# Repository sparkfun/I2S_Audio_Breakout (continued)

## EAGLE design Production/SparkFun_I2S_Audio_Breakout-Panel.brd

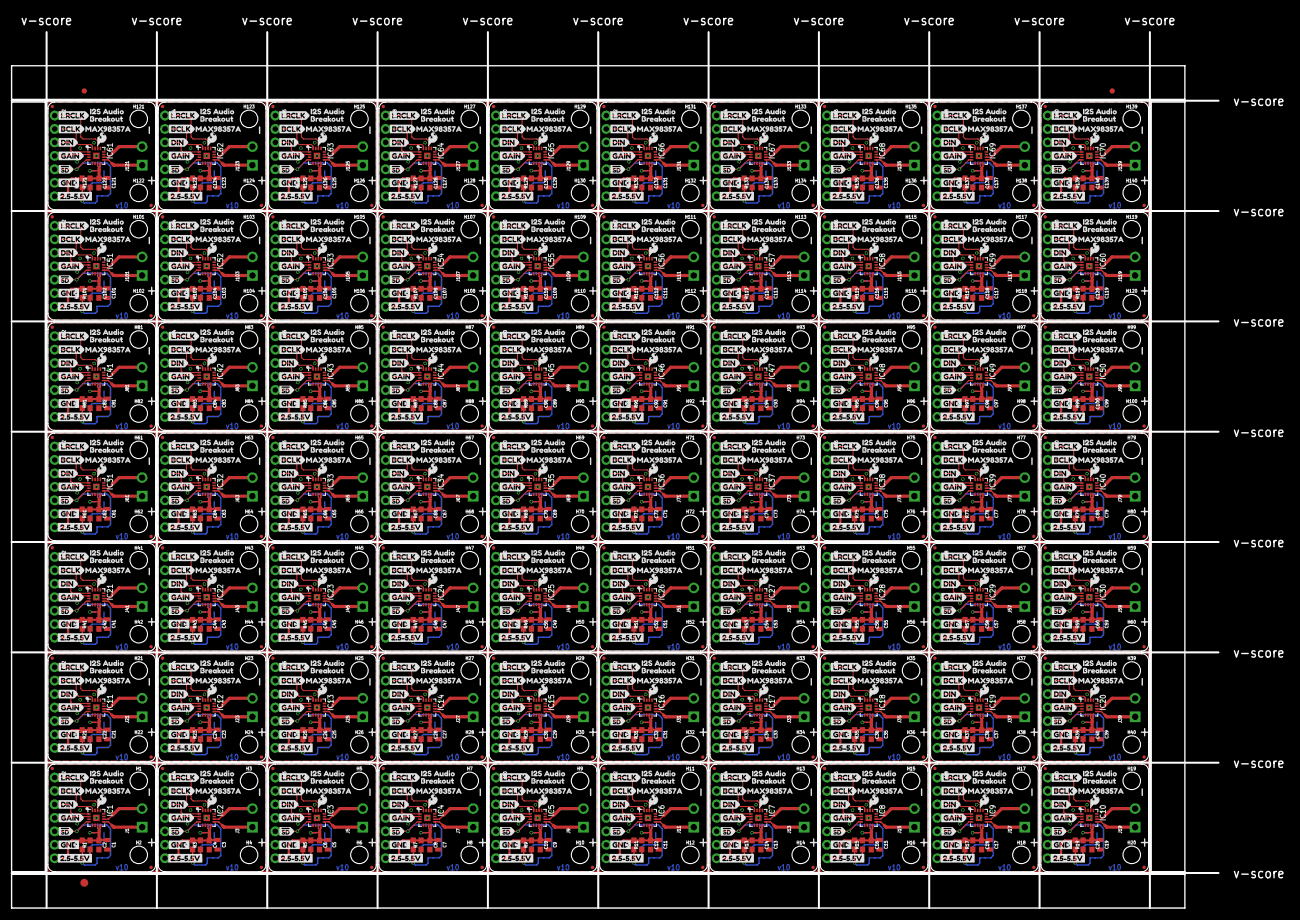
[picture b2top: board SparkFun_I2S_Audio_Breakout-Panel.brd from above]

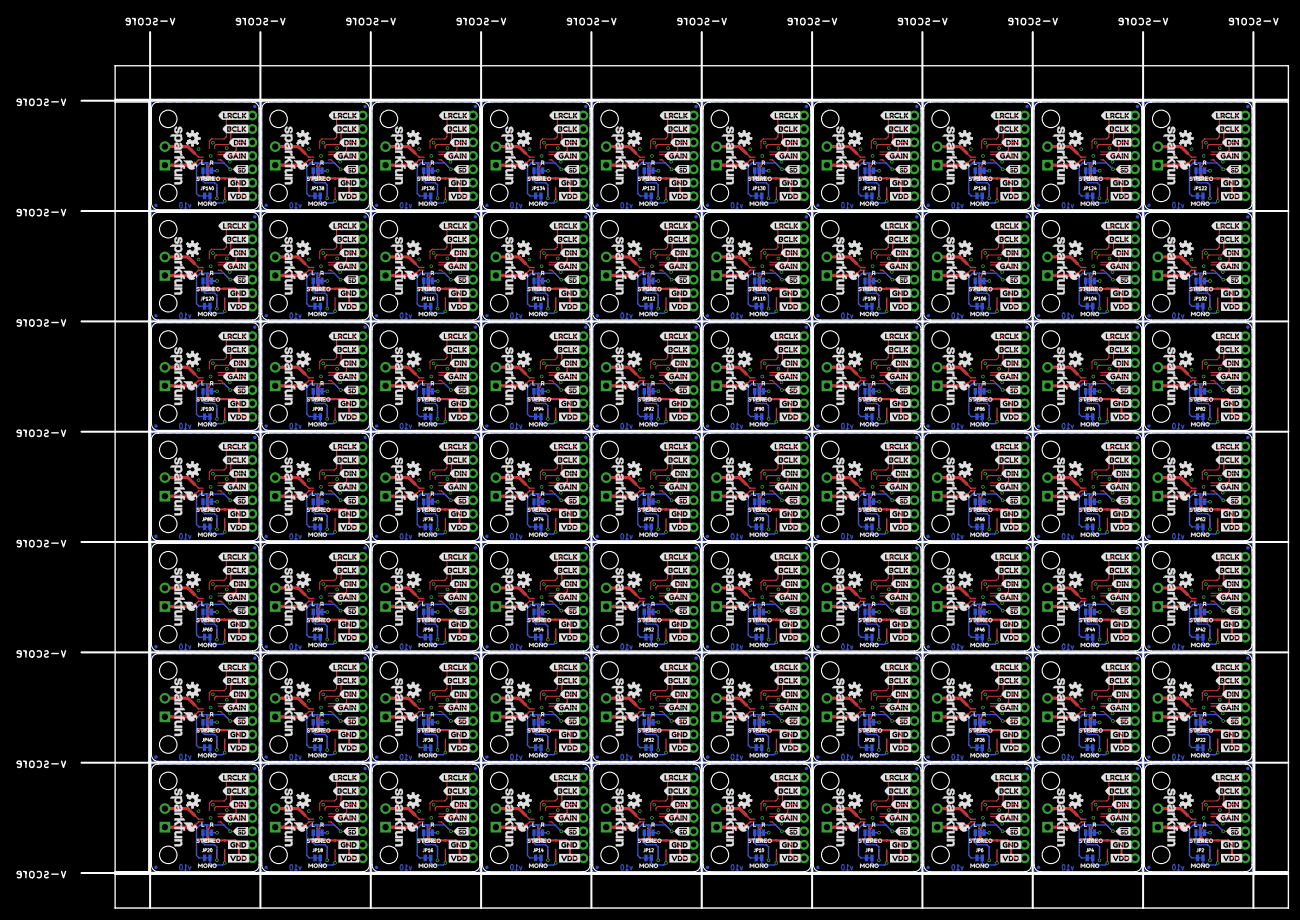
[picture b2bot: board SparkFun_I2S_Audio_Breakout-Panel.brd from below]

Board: 2 copper layers, 227.8 x 165.4 mm, 2733 parts (1190 on the bottom side), 770 nets.

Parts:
C1, C3, C5, C7, C9, C11, C13, C15, C17, C19, C21, C23, C25, C27, C29, C31, C33, C35, C37, C39, C41, C43, C45, C47, C49, C51, C53, C55, C57, C59, C61, C63, C65, C67, C69, C71, C73, C75, C77, C79, C81, C83, C85, C87, C89, C91, C93, C95, C97, C99, C101, C103, C105, C107, C109, C111, C113, C115, C117, C119, C121, C123, C125, C127, C129, C131, C133, C135, C137, C139: 10uF; 0805
C2, C4, C6, C8, C10, C12, C14, C16, C18, C20, C22, C24, C26, C28, C30, C32, C34, C36, C38, C40, C42, C44, C46, C48, C50, C52, C54, C56, C58, C60, C62, C64, C66, C68, C70, C72, C74, C76, C78, C80, C82, C84, C86, C88, C90, C92, C94, C96, C98, C100, C102, C104, C106, C108, C110, C112, C114, C116, C118, C120, C122, C124, C126, C128, C130, C132, C134, C136, C138, C140: 0.1uF; 0603
E$1, E$2: FIDUCIAL-1X2
E$3: FIDUCIAL-1.5X3
FD1, FD2, FD3, FD4, FD5, FD6, FD7, FD8, FD9, FD10, FD11, FD12, FD13, FD14, FD15, FD16, FD17, FD18, FD19, FD20, FD21, FD22, FD23, FD24, FD25, FD26, FD27, FD28, FD29, FD30, FD31, FD32, FD33, FD34, FD35, FD36, FD37, FD38, FD39, FD40, FD41, FD42, FD43, FD44, FD45, FD46, FD47, FD48, FD49, FD50, FD51, FD52, FD53, FD54, FD55, FD56, FD57, FD58, FD59, FD60, FD61, FD62, FD63, FD64, FD65, FD66, FD67, FD68, FD69, FD70, FD71, FD72, FD73, FD74, FD75, FD76, FD77, FD78, FD79, FD80, FD81, FD82, FD83, FD84, FD85, FD86, FD87, FD88, FD89, FD90, FD91, FD92, FD93, FD94, FD95, FD96, FD97, FD98, FD99, FD100, FD101, FD102, FD103, FD104, FD105, FD106, FD107, FD108, FD109, FD110, FD111, FD112, FD113, FD114, FD115, FD116, FD117, FD118, FD119, FD120, FD121, FD122, FD123, FD124, FD125, FD126, FD127, FD128, FD129, FD130, FD131, FD132, FD133, FD134, FD135, FD136, FD137, FD138, FD139, FD140, FD141, FD142, FD143, FD144, FD145, FD146, FD147, FD148, FD149, FD150, FD151, FD152, FD153, FD154, FD155, FD156, FD157, FD158, FD159, FD160, FD161, FD162, FD163, FD164, FD165, FD166, FD167, FD168, FD169, FD170, FD171, FD172, FD173, FD174, FD175, FD176, FD177, FD178, FD179, FD180, FD181, FD182, FD183, FD184, FD185, FD186, FD187, FD188, FD189, FD190, FD191, FD192, FD193, FD194, FD195, FD196, FD197, FD198, FD199, FD200, FD201, FD202, FD203, FD204, FD205, FD206, FD207, FD208, FD209, FD210, FD211, FD212, FD213, FD214, FD215, FD216, FD217, FD218, FD219, FD220, FD221, FD222, FD223, FD224, FD225, FD226, FD227, FD228, FD229, FD230, FD231, FD232, FD233, FD234, FD235, FD236, FD237, FD238, FD239, FD240, FD241, FD242, FD243, FD244, FD245, FD246, FD247, FD248, FD249, FD250, FD251, FD252, FD253, FD254, FD255, FD256, FD257, FD258, FD259, FD260, FD261, FD262, FD263, FD264, FD265, FD266, FD267, FD268, FD269, FD270, FD271, FD272, FD273, FD274, FD275, FD276, FD277, FD278, FD279, FD280: FIDUCIALUFIDUCIAL; FIDUCIAL-MICRO
H1, H2, H3, H4, H5, H6, H7, H8, H9, H10, H11, H12, H13, H14, H15, H16, H17, H18, H19, H20, H21, H22, H23, H24, H25, H26, H27, H28, H29, H30, H31, H32, H33, H34, H35, H36, H37, H38, H39, H40, H41, H42, H43, H44, H45, H46, H47, H48, H49, H50, H51, H52, H53, H54, H55, H56, H57, H58, H59, H60, H61, H62, H63, H64, H65, H66, H67, H68, H69, H70, H71, H72, H73, H74, H75, H76, H77, H78, H79, H80, H81, H82, H83, H84, H85, H86, H87, H88, H89, H90, H91, H92, H93, H94, H95, H96, H97, H98, H99, H100, H101, H102, H103, H104, H105, H106, H107, H108, H109, H110, H111, H112, H113, H114, H115, H116, H117, H118, H119, H120, H121, H122, H123, H124, H125, H126, H127, H128, H129, H130, H131, H132, H133, H134, H135, H136, H137, H138, H139, H140: STAND-OFF
IC1, IC2, IC3, IC4, IC5, IC6, IC7, IC8, IC9, IC10, IC11, IC12, IC13, IC14, IC15, IC16, IC17, IC18, IC19, IC20, IC21, IC22, IC23, IC24, IC25, IC26, IC27, IC28, IC29, IC30, IC31, IC32, IC33, IC34, IC35, IC36, IC37, IC38, IC39, IC40, IC41, IC42, IC43, IC44, IC45, IC46, IC47, IC48, IC49, IC50, IC51, IC52, IC53, IC54, IC55, IC56, IC57, IC58, IC59, IC60, IC61, IC62, IC63, IC64, IC65, IC66, IC67, IC68, IC69, IC70: MAX98375A; TQFN-16
J1, J3, J5, J7, J9, J11, J13, J15, J17, J19, J21, J23, J25, J27, J29, J31, J33, J35, J37, J39, J41, J43, J45, J47, J49, J51, J53, J55, J57, J59, J61, J63, J65, J67, J69, J71, J73, J75, J77, J79, J81, J83, J85, J87, J89, J91, J93, J95, J97, J99, J101, J103, J105, J107, J109, J111, J113, J115, J117, J119, J121, J123, J125, J127, J129, J131, J133, J135, J137, J139: SCREWTERMINAL-3.5MM-2-NS
J2, J4, J6, J8, J10, J12, J14, J16, J18, J20, J22, J24, J26, J28, J30, J32, J34, J36, J38, J40, J42, J44, J46, J48, J50, J52, J54, J56, J58, J60, J62, J64, J66, J68, J70, J72, J74, J76, J78, J80, J82, J84, J86, J88, J90, J92, J94, J96, J98, J100, J102, J104, J106, J108, J110, J112, J114, J116, J118, J120, J122, J124, J126, J128, J130, J132, J134, J136, J138, J140: 1X07_NO_SILK
JP1, JP3, JP5, JP7, JP9, JP11, JP13, JP15, JP17, JP19, JP21, JP23, JP25, JP27, JP29, JP31, JP33, JP35, JP37, JP39, JP41, JP43, JP45, JP47, JP49, JP51, JP53, JP55, JP57, JP59, JP61, JP63, JP65, JP67, JP69, JP71, JP73, JP75, JP77, JP79, JP81, JP83, JP85, JP87, JP89, JP91, JP93, JP95, JP97, JP99, JP101, JP103, JP105, JP107, JP109, JP111, JP113, JP115, JP117, JP119, JP121, JP123, JP125, JP127, JP129, JP131, JP133, JP135, JP137, JP139: SMT-JUMPER_3_NO_NO-SILK
JP2, JP4, JP6, JP8, JP10, JP12, JP14, JP16, JP18, JP20, JP22, JP24, JP26, JP28, JP30, JP32, JP34, JP36, JP38, JP40, JP42, JP44, JP46, JP48, JP50, JP52, JP54, JP56, JP58, JP60, JP62, JP64, JP66, JP68, JP70, JP72, JP74, JP76, JP78, JP80, JP82, JP84, JP86, JP88, JP90, JP92, JP94, JP96, JP98, JP100, JP102, JP104, JP106, JP108, JP110, JP112, JP114, JP116, JP118, JP120, JP122, JP124, JP126, JP128, JP130, JP132, JP134, JP136, JP138, JP140: SMT-JUMPER_2_NC_TRACE_NO-SILK
LOGO1, LOGO3, LOGO5, LOGO7, LOGO9, LOGO11, LOGO13, LOGO15, LOGO17, LOGO19, LOGO21, LOGO23, LOGO25, LOGO27, LOGO29, LOGO31, LOGO33, LOGO35, LOGO37, LOGO39, LOGO41, LOGO43, LOGO45, LOGO47, LOGO49, LOGO51, LOGO53, LOGO55, LOGO57, LOGO59, LOGO61, LOGO63, LOGO65, LOGO67, LOGO69, LOGO71, LOGO73, LOGO75, LOGO77, LOGO79, LOGO81, LOGO83, LOGO85, LOGO87, LOGO89, LOGO91, LOGO93, LOGO95, LOGO97, LOGO99, LOGO101, LOGO103, LOGO105, LOGO107, LOGO109, LOGO111, LOGO113, LOGO115, LOGO117, LOGO119, LOGO121, LOGO123, LOGO125, LOGO127, LOGO129, LOGO131, LOGO133, LOGO135, LOGO137, LOGO139: SFE_LOGO_NAME_FLAME.1_INCH; SFE_LOGO_NAME_FLAME_.1
LOGO2, LOGO4, LOGO6, LOGO8, LOGO10, LOGO12, LOGO14, LOGO16, LOGO18, LOGO20, LOGO22, LOGO24, LOGO26, LOGO28, LOGO30, LOGO32, LOGO34, LOGO36, LOGO38, LOGO40, LOGO42, LOGO44, LOGO46, LOGO48, LOGO50, LOGO52, LOGO54, LOGO56, LOGO58, LOGO60, LOGO62, LOGO64, LOGO66, LOGO68, LOGO70, LOGO72, LOGO74, LOGO76, LOGO78, LOGO80, LOGO82, LOGO84, LOGO86, LOGO88, LOGO90, LOGO92, LOGO94, LOGO96, LOGO98, LOGO100, LOGO102, LOGO104, LOGO106, LOGO108, LOGO110, LOGO112, LOGO114, LOGO116, LOGO118, LOGO120, LOGO122, LOGO124, LOGO126, LOGO128, LOGO130, LOGO132, LOGO134, LOGO136, LOGO138, LOGO140: OSHW-LOGOS; OSHW-LOGO-S
R1, R3, R5, R7, R9, R11, R13, R15, R17, R19, R21, R23, R25, R27, R29, R31, R33, R35, R37, R39, R41, R43, R45, R47, R49, R51, R53, R55, R57, R59, R61, R63, R65, R67, R69, R71, R73, R75, R77, R79, R81, R83, R85, R87, R89, R91, R93, R95, R97, R99, R101, R103, R105, R107, R109, R111, R113, R115, R117, R119, R121, R123, R125, R127, R129, R131, R133, R135, R137, R139: 300k; 0603
R2, R4, R6, R8, R10, R12, R14, R16, R18, R20, R22, R24, R26, R28, R30, R32, R34, R36, R38, R40, R42, R44, R46, R48, R50, R52, R54, R56, R58, R60, R62, R64, R66, R68, R70, R72, R74, R76, R78, R80, R82, R84, R86, R88, R90, R92, R94, R96, R98, R100, R102, R104, R106, R108, R110, R112, R114, R116, R118, R120, R122, R124, R126, R128, R130, R132, R134, R136, R138, R140: 1M; 0603
U$1, U$24, U$46, U$68, U$90, U$112, U$134, U$156, U$178, U$200, U$222, U$244, U$266, U$288, U$310, U$332, U$354, U$376, U$398, U$420, U$442, U$464, U$486, U$508, U$530, U$552, U$574, U$596, U$618, U$640, U$662, U$684, U$706, U$728, U$750, U$772, U$794, U$816, U$838, U$860, U$882, U$904, U$926, U$948, U$970, U$992, U$1014, U$1036, U$1058, U$1080, U$1102, U$1124, U$1146, U$1168, U$1190, U$1212, U$1234, U$1256, U$1278, U$1300, U$1322, U$1344, U$1366, U$1388, U$1410, U$1432, U$1454, U$1476, U$1498, U$1520: 2#5#5#5V13
U$2, U$23, U$25, U$39, U$47, U$61, U$69, U$83, U$91, U$105, U$113, U$127, U$135, U$149, U$157, U$171, U$179, U$193, U$201, U$215, U$223, U$237, U$245, U$259, U$267, U$281, U$289, U$303, U$311, U$325, U$333, U$347, U$355, U$369, U$377, U$391, U$399, U$413, U$421, U$435, U$443, U$457, U$465, U$479, U$487, U$501, U$509, U$523, U$531, U$545, U$553, U$567, U$575, U$589, U$597, U$611, U$619, U$633, U$641, U$655, U$663, U$677, U$685, U$699, U$707, U$721, U$729, U$743, U$751, U$765, U$773, U$787, U$795, U$809, U$817, U$831, U$839, U$853, U$861, U$875, U$883, U$897, U$905, U$919, U$927, U$941, U$949, U$963, U$971, U$985, U$993, U$1007, U$1015, U$1029, U$1037, U$1051, U$1059, U$1073, U$1081, U$1095, U$1103, U$1117, U$1125, U$1139, U$1147, U$1161, U$1169, U$1183, U$1191, U$1205, U$1213, U$1227, U$1235, U$1249, U$1257, U$1271, U$1279, U$1293, U$1301, U$1315, U$1323, U$1337, U$1345, U$1359, U$1367, U$1381, U$1389, U$1403, U$1411, U$1425, U$1433, U$1447, U$1455, U$1469, U$1477, U$1491, U$1499, U$1513, U$1521, U$1535: GND9
U$3, U$26, U$48, U$70, U$92, U$114, U$136, U$158, U$180, U$202, U$224, U$246, U$268, U$290, U$312, U$334, U$356, U$378, U$400, U$422, U$444, U$466, U$488, U$510, U$532, U$554, U$576, U$598, U$620, U$642, U$664, U$686, U$708, U$730, U$752, U$774, U$796, U$818, U$840, U$862, U$884, U$906, U$928, U$950, U$972, U$994, U$1016, U$1038, U$1060, U$1082, U$1104, U$1126, U$1148, U$1170, U$1192, U$1214, U$1236, U$1258, U$1280, U$1302, U$1324, U$1346, U$1368, U$1390, U$1412, U$1434, U$1456, U$1478, U$1500, U$1522: #SD7
U$4, U$27, U$49, U$71, U$93, U$115, U$137, U$159, U$181, U$203, U$225, U$247, U$269, U$291, U$313, U$335, U$357, U$379, U$401, U$423, U$445, U$467, U$489, U$511, U$533, U$555, U$577, U$599, U$621, U$643, U$665, U$687, U$709, U$731, U$753, U$775, U$797, U$819, U$841, U$863, U$885, U$907, U$929, U$951, U$973, U$995, U$1017, U$1039, U$1061, U$1083, U$1105, U$1127, U$1149, U$1171, U$1193, U$1215, U$1237, U$1259, U$1281, U$1303, U$1325, U$1347, U$1369, U$1391, U$1413, U$1435, U$1457, U$1479, U$1501, U$1523: GAIN6
U$5, U$28, U$50, U$72, U$94, U$116, U$138, U$160, U$182, U$204, U$226, U$248, U$270, U$292, U$314, U$336, U$358, U$380, U$402, U$424, U$446, U$468, U$490, U$512, U$534, U$556, U$578, U$600, U$622, U$644, U$666, U$688, U$710, U$732, U$754, U$776, U$798, U$820, U$842, U$864, U$886, U$908, U$930, U$952, U$974, U$996, U$1018, U$1040, U$1062, U$1084, U$1106, U$1128, U$1150, U$1172, U$1194, U$1216, U$1238, U$1260, U$1282, U$1304, U$1326, U$1348, U$1370, U$1392, U$1414, U$1436, U$1458, U$1480, U$1502, U$1524: DIN5
U$6, U$29, U$51, U$73, U$95, U$117, U$139, U$161, U$183, U$205, U$227, U$249, U$271, U$293, U$315, U$337, U$359, U$381, U$403, U$425, U$447, U$469, U$491, U$513, U$535, U$557, U$579, U$601, U$623, U$645, U$667, U$689, U$711, U$733, U$755, U$777, U$799, U$821, U$843, U$865, U$887, U$909, U$931, U$953, U$975, U$997, U$1019, U$1041, U$1063, U$1085, U$1107, U$1129, U$1151, U$1173, U$1195, U$1217, U$1239, U$1261, U$1283, U$1305, U$1327, U$1349, U$1371, U$1393, U$1415, U$1437, U$1459, U$1481, U$1503, U$1525: BCLK4
U$7, U$30, U$52, U$74, U$96, U$118, U$140, U$162, U$184, U$206, U$228, U$250, U$272, U$294, U$316, U$338, U$360, U$382, U$404, U$426, U$448, U$470, U$492, U$514, U$536, U$558, U$580, U$602, U$624, U$646, U$668, U$690, U$712, U$734, U$756, U$778, U$800, U$822, U$844, U$866, U$888, U$910, U$932, U$954, U$976, U$998, U$1020, U$1042, U$1064, U$1086, U$1108, U$1130, U$1152, U$1174, U$1196, U$1218, U$1240, U$1262, U$1284, U$1306, U$1328, U$1350, U$1372, U$1394, U$1416, U$1438, U$1460, U$1482, U$1504, U$1526: LRCLK3
U$8, U$31, U$53, U$75, U$97, U$119, U$141, U$163, U$185, U$207, U$229, U$251, U$273, U$295, U$317, U$339, U$361, U$383, U$405, U$427, U$449, U$471, U$493, U$515, U$537, U$559, U$581, U$603, U$625, U$647, U$669, U$691, U$713, U$735, U$757, U$779, U$801, U$823, U$845, U$867, U$889, U$911, U$933, U$955, U$977, U$999, U$1021, U$1043, U$1065, U$1087, U$1109, U$1131, U$1153, U$1175, U$1197, U$1219, U$1241, U$1263, U$1285, U$1307, U$1329, U$1351, U$1373, U$1395, U$1417, U$1439, U$1461, U$1483, U$1505, U$1527: I2S_AUDIO0
U$9, U$32, U$54, U$76, U$98, U$120, U$142, U$164, U$186, U$208, U$230, U$252, U$274, U$296, U$318, U$340, U$362, U$384, U$406, U$428, U$450, U$472, U$494, U$516, U$538, U$560, U$582, U$604, U$626, U$648, U$670, U$692, U$714, U$736, U$758, U$780, U$802, U$824, U$846, U$868, U$890, U$912, U$934, U$956, U$978, U$1000, U$1022, U$1044, U$1066, U$1088, U$1110, U$1132, U$1154, U$1176, U$1198, U$1220, U$1242, U$1264, U$1286, U$1308, U$1330, U$1352, U$1374, U$1396, U$1418, U$1440, U$1462, U$1484, U$1506, U$1528: BREAKOUT1
U$10, U$33, U$55, U$77, U$99, U$121, U$143, U$165, U$187, U$209, U$231, U$253, U$275, U$297, U$319, U$341, U$363, U$385, U$407, U$429, U$451, U$473, U$495, U$517, U$539, U$561, U$583, U$605, U$627, U$649, U$671, U$693, U$715, U$737, U$759, U$781, U$803, U$825, U$847, U$869, U$891, U$913, U$935, U$957, U$979, U$1001, U$1023, U$1045, U$1067, U$1089, U$1111, U$1133, U$1155, U$1177, U$1199, U$1221, U$1243, U$1265, U$1287, U$1309, U$1331, U$1353, U$1375, U$1397, U$1419, U$1441, U$1463, U$1485, U$1507, U$1529: MAX98357A2
U$11, U$40, U$62, U$84, U$106, U$128, U$150, U$172, U$194, U$216, U$238, U$260, U$282, U$304, U$326, U$348, U$370, U$392, U$414, U$436, U$458, U$480, U$502, U$524, U$546, U$568, U$590, U$612, U$634, U$656, U$678, U$700, U$722, U$744, U$766, U$788, U$810, U$832, U$854, U$876, U$898, U$920, U$942, U$964, U$986, U$1008, U$1030, U$1052, U$1074, U$1096, U$1118, U$1140, U$1162, U$1184, U$1206, U$1228, U$1250, U$1272, U$1294, U$1316, U$1338, U$1360, U$1382, U$1404, U$1426, U$1448, U$1470, U$1492, U$1514, U$1536: LRCLK0
U$12, U$41, U$63, U$85, U$107, U$129, U$151, U$173, U$195, U$217, U$239, U$261, U$283, U$305, U$327, U$349, U$371, U$393, U$415, U$437, U$459, U$481, U$503, U$525, U$547, U$569, U$591, U$613, U$635, U$657, U$679, U$701, U$723, U$745, U$767, U$789, U$811, U$833, U$855, U$877, U$899, U$921, U$943, U$965, U$987, U$1009, U$1031, U$1053, U$1075, U$1097, U$1119, U$1141, U$1163, U$1185, U$1207, U$1229, U$1251, U$1273, U$1295, U$1317, U$1339, U$1361, U$1383, U$1405, U$1427, U$1449, U$1471, U$1493, U$1515, U$1537: BCLK1
U$13, U$42, U$64, U$86, U$108, U$130, U$152, U$174, U$196, U$218, U$240, U$262, U$284, U$306, U$328, U$350, U$372, U$394, U$416, U$438, U$460, U$482, U$504, U$526, U$548, U$570, U$592, U$614, U$636, U$658, U$680, U$702, U$724, U$746, U$768, U$790, U$812, U$834, U$856, U$878, U$900, U$922, U$944, U$966, U$988, U$1010, U$1032, U$1054, U$1076, U$1098, U$1120, U$1142, U$1164, U$1186, U$1208, U$1230, U$1252, U$1274, U$1296, U$1318, U$1340, U$1362, U$1384, U$1406, U$1428, U$1450, U$1472, U$1494, U$1516, U$1538: DIN2
U$14, U$43, U$65, U$87, U$109, U$131, U$153, U$175, U$197, U$219, U$241, U$263, U$285, U$307, U$329, U$351, U$373, U$395, U$417, U$439, U$461, U$483, U$505, U$527, U$549, U$571, U$593, U$615, U$637, U$659, U$681, U$703, U$725, U$747, U$769, U$791, U$813, U$835, U$857, U$879, U$901, U$923, U$945, U$967, U$989, U$1011, U$1033, U$1055, U$1077, U$1099, U$1121, U$1143, U$1165, U$1187, U$1209, U$1231, U$1253, U$1275, U$1297, U$1319, U$1341, U$1363, U$1385, U$1407, U$1429, U$1451, U$1473, U$1495, U$1517, U$1539: GAIN3
U$15, U$21, U$45, U$67, U$89, U$111, U$133, U$155, U$177, U$199, U$221, U$243, U$265, U$287, U$309, U$331, U$353, U$375, U$397, U$419, U$441, U$463, U$485, U$507, U$529, U$551, U$573, U$595, U$617, U$639, U$661, U$683, U$705, U$727, U$749, U$771, U$793, U$815, U$837, U$859, U$881, U$903, U$925, U$947, U$969, U$991, U$1013, U$1035, U$1057, U$1079, U$1101, U$1123, U$1145, U$1167, U$1189, U$1211, U$1233, U$1255, U$1277, U$1299, U$1321, U$1343, U$1365, U$1387, U$1409, U$1431, U$1453, U$1475, U$1497, U$1519: SFE_LOGO_FLAME_.1
U$16, U$35, U$57, U$79, U$101, U$123, U$145, U$167, U$189, U$211, U$233, U$255, U$277, U$299, U$321, U$343, U$365, U$387, U$409, U$431, U$453, U$475, U$497, U$519, U$541, U$563, U$585, U$607, U$629, U$651, U$673, U$695, U$717, U$739, U$761, U$783, U$805, U$827, U$849, U$871, U$893, U$915, U$937, U$959, U$981, U$1003, U$1025, U$1047, U$1069, U$1091, U$1113, U$1135, U$1157, U$1179, U$1201, U$1223, U$1245, U$1267, U$1289, U$1311, U$1333, U$1355, U$1377, U$1399, U$1421, U$1443, U$1465, U$1487, U$1509, U$1531: MONO12
U$17, U$37, U$59, U$81, U$103, U$125, U$147, U$169, U$191, U$213, U$235, U$257, U$279, U$301, U$323, U$345, U$367, U$389, U$411, U$433, U$455, U$477, U$499, U$521, U$543, U$565, U$587, U$609, U$631, U$653, U$675, U$697, U$719, U$741, U$763, U$785, U$807, U$829, U$851, U$873, U$895, U$917, U$939, U$961, U$983, U$1005, U$1027, U$1049, U$1071, U$1093, U$1115, U$1137, U$1159, U$1181, U$1203, U$1225, U$1247, U$1269, U$1291, U$1313, U$1335, U$1357, U$1379, U$1401, U$1423, U$1445, U$1467, U$1489, U$1511, U$1533: L10
U$18, U$38, U$60, U$82, U$104, U$126, U$148, U$170, U$192, U$214, U$236, U$258, U$280, U$302, U$324, U$346, U$368, U$390, U$412, U$434, U$456, U$478, U$500, U$522, U$544, U$566, U$588, U$610, U$632, U$654, U$676, U$698, U$720, U$742, U$764, U$786, U$808, U$830, U$852, U$874, U$896, U$918, U$940, U$962, U$984, U$1006, U$1028, U$1050, U$1072, U$1094, U$1116, U$1138, U$1160, U$1182, U$1204, U$1226, U$1248, U$1270, U$1292, U$1314, U$1336, U$1358, U$1380, U$1402, U$1424, U$1446, U$1468, U$1490, U$1512, U$1534: R11
U$19, U$36, U$58, U$80, U$102, U$124, U$146, U$168, U$190, U$212, U$234, U$256, U$278, U$300, U$322, U$344, U$366, U$388, U$410, U$432, U$454, U$476, U$498, U$520, U$542, U$564, U$586, U$608, U$630, U$652, U$674, U$696, U$718, U$740, U$762, U$784, U$806, U$828, U$850, U$872, U$894, U$916, U$938, U$960, U$982, U$1004, U$1026, U$1048, U$1070, U$1092, U$1114, U$1136, U$1158, U$1180, U$1202, U$1224, U$1246, U$1268, U$1290, U$1312, U$1334, U$1356, U$1378, U$1400, U$1422, U$1444, U$1466, U$1488, U$1510, U$1532: STEREO14
U$20, U$44, U$66, U$88, U$110, U$132, U$154, U$176, U$198, U$220, U$242, U$264, U$286, U$308, U$330, U$352, U$374, U$396, U$418, U$440, U$462, U$484, U$506, U$528, U$550, U$572, U$594, U$616, U$638, U$660, U$682, U$704, U$726, U$748, U$770, U$792, U$814, U$836, U$858, U$880, U$902, U$924, U$946, U$968, U$990, U$1012, U$1034, U$1056, U$1078, U$1100, U$1122, U$1144, U$1166, U$1188, U$1210, U$1232, U$1254, U$1276, U$1298, U$1320, U$1342, U$1364, U$1386, U$1408, U$1430, U$1452, U$1474, U$1496, U$1518, U$1540: #SD4
U$22, U$34, U$56, U$78, U$100, U$122, U$144, U$166, U$188, U$210, U$232, U$254, U$276, U$298, U$320, U$342, U$364, U$386, U$408, U$430, U$452, U$474, U$496, U$518, U$540, U$562, U$584, U$606, U$628, U$650, U$672, U$694, U$716, U$738, U$760, U$782, U$804, U$826, U$848, U$870, U$892, U$914, U$936, U$958, U$980, U$1002, U$1024, U$1046, U$1068, U$1090, U$1112, U$1134, U$1156, U$1178, U$1200, U$1222, U$1244, U$1266, U$1288, U$1310, U$1332, U$1354, U$1376, U$1398, U$1420, U$1442, U$1464, U$1486, U$1508, U$1530: VDD8

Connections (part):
!SD: IC1.P$4, J2.5, JP1.2, JP2.1
!SD1: IC2.P$4, J4.5, JP3.2, JP4.1
!SD2: IC3.P$4, J6.5, JP5.2, JP6.1
!SD3: IC4.P$4, J8.5, JP7.2, JP8.1
!SD4: IC5.P$4, J10.5, JP9.2, JP10.1
!SD5: IC6.P$4, J12.5, JP11.2, JP12.1
!SD6: IC7.P$4, J14.5, JP13.2, JP14.1
!SD7: IC8.P$4, J16.5, JP15.2, JP16.1
!SD8: IC9.P$4, J18.5, JP17.2, JP18.1
!SD9: IC10.P$4, J20.5, JP19.2, JP20.1
!SD10: IC11.P$4, J22.5, JP21.2, JP22.1
!SD11: IC12.P$4, J24.5, JP23.2, JP24.1
!SD12: IC13.P$4, J26.5, JP25.2, JP26.1
!SD13: IC14.P$4, J28.5, JP27.2, JP28.1
!SD14: IC15.P$4, J30.5, JP29.2, JP30.1
!SD15: IC16.P$4, J32.5, JP31.2, JP32.1
!SD16: IC17.P$4, J34.5, JP33.2, JP34.1
!SD17: IC18.P$4, J36.5, JP35.2, JP36.1
!SD18: IC19.P$4, J38.5, JP37.2, JP38.1
!SD19: IC20.P$4, J40.5, JP39.2, JP40.1
!SD20: IC21.P$4, J42.5, JP41.2, JP42.1
!SD21: IC22.P$4, J44.5, JP43.2, JP44.1
!SD22: IC23.P$4, J46.5, JP45.2, JP46.1
!SD23: IC24.P$4, J48.5, JP47.2, JP48.1
!SD24: IC25.P$4, J50.5, JP49.2, JP50.1
!SD25: IC26.P$4, J52.5, JP51.2, JP52.1
!SD26: IC27.P$4, J54.5, JP53.2, JP54.1
!SD27: IC28.P$4, J56.5, JP55.2, JP56.1
!SD28: IC29.P$4, J58.5, JP57.2, JP58.1
!SD29: IC30.P$4, J60.5, JP59.2, JP60.1
!SD30: IC31.P$4, J62.5, JP61.2, JP62.1
!SD31: IC32.P$4, J64.5, JP63.2, JP64.1
!SD32: IC33.P$4, J66.5, JP65.2, JP66.1
!SD33: IC34.P$4, J68.5, JP67.2, JP68.1
!SD34: IC35.P$4, J70.5, JP69.2, JP70.1
!SD35: IC36.P$4, J72.5, JP71.2, JP72.1
!SD36: IC37.P$4, J74.5, JP73.2, JP74.1
!SD37: IC38.P$4, J76.5, JP75.2, JP76.1
!SD38: IC39.P$4, J78.5, JP77.2, JP78.1
!SD39: IC40.P$4, J80.5, JP79.2, JP80.1
!SD40: IC41.P$4, J82.5, JP81.2, JP82.1
!SD41: IC42.P$4, J84.5, JP83.2, JP84.1
!SD42: IC43.P$4, J86.5, JP85.2, JP86.1
!SD43: IC44.P$4, J88.5, JP87.2, JP88.1
!SD44: IC45.P$4, J90.5, JP89.2, JP90.1
!SD45: IC46.P$4, J92.5, JP91.2, JP92.1
!SD46: IC47.P$4, J94.5, JP93.2, JP94.1
!SD47: IC48.P$4, J96.5, JP95.2, JP96.1
!SD48: IC49.P$4, J98.5, JP97.2, JP98.1
!SD49: IC50.P$4, J100.5, JP99.2, JP100.1
!SD50: IC51.P$4, J102.5, JP101.2, JP102.1
!SD51: IC52.P$4, J104.5, JP103.2, JP104.1
!SD52: IC53.P$4, J106.5, JP105.2, JP106.1
!SD53: IC54.P$4, J108.5, JP107.2, JP108.1
!SD54: IC55.P$4, J110.5, JP109.2, JP110.1
!SD55: IC56.P$4, J112.5, JP111.2, JP112.1
!SD56: IC57.P$4, J114.5, JP113.2, JP114.1
!SD57: IC58.P$4, J116.5, JP115.2, JP116.1
!SD58: IC59.P$4, J118.5, JP117.2, JP118.1
!SD59: IC60.P$4, J120.5, JP119.2, JP120.1
!SD60: IC61.P$4, J122.5, JP121.2, JP122.1
!SD61: IC62.P$4, J124.5, JP123.2, JP124.1
!SD62: IC63.P$4, J126.5, JP125.2, JP126.1
!SD63: IC64.P$4, J128.5, JP127.2, JP128.1
!SD64: IC65.P$4, J130.5, JP129.2, JP130.1
!SD65: IC66.P$4, J132.5, JP131.2, JP132.1
!SD66: IC67.P$4, J134.5, JP133.2, JP134.1
!SD67: IC68.P$4, J136.5, JP135.2, JP136.1
!SD68: IC69.P$4, J138.5, JP137.2, JP138.1
!SD69: IC70.P$4, J140.5, JP139.2, JP140.1
BCLK: IC1.P$16, J2.2
BCLK1: IC2.P$16, J4.2
BCLK2: IC3.P$16, J6.2
BCLK3: IC4.P$16, J8.2
BCLK4: IC5.P$16, J10.2
BCLK5: IC6.P$16, J12.2
BCLK6: IC7.P$16, J14.2
BCLK7: IC8.P$16, J16.2
BCLK8: IC9.P$16, J18.2
BCLK9: IC10.P$16, J20.2
BCLK10: IC11.P$16, J22.2
BCLK11: IC12.P$16, J24.2
BCLK12: IC13.P$16, J26.2
BCLK13: IC14.P$16, J28.2
BCLK14: IC15.P$16, J30.2
BCLK15: IC16.P$16, J32.2
BCLK16: IC17.P$16, J34.2
BCLK17: IC18.P$16, J36.2
BCLK18: IC19.P$16, J38.2
BCLK19: IC20.P$16, J40.2
BCLK20: IC21.P$16, J42.2
BCLK21: IC22.P$16, J44.2
BCLK22: IC23.P$16, J46.2
BCLK23: IC24.P$16, J48.2
BCLK24: IC25.P$16, J50.2
BCLK25: IC26.P$16, J52.2
BCLK26: IC27.P$16, J54.2
BCLK27: IC28.P$16, J56.2
BCLK28: IC29.P$16, J58.2
BCLK29: IC30.P$16, J60.2
BCLK30: IC31.P$16, J62.2
BCLK31: IC32.P$16, J64.2
BCLK32: IC33.P$16, J66.2
BCLK33: IC34.P$16, J68.2
BCLK34: IC35.P$16, J70.2
BCLK35: IC36.P$16, J72.2
BCLK36: IC37.P$16, J74.2
BCLK37: IC38.P$16, J76.2
BCLK38: IC39.P$16, J78.2
BCLK39: IC40.P$16, J80.2
BCLK40: IC41.P$16, J82.2
BCLK41: IC42.P$16, J84.2
BCLK42: IC43.P$16, J86.2
BCLK43: IC44.P$16, J88.2
BCLK44: IC45.P$16, J90.2
BCLK45: IC46.P$16, J92.2
BCLK46: IC47.P$16, J94.2
BCLK47: IC48.P$16, J96.2
BCLK48: IC49.P$16, J98.2
BCLK49: IC50.P$16, J100.2
BCLK50: IC51.P$16, J102.2
BCLK51: IC52.P$16, J104.2
BCLK52: IC53.P$16, J106.2
BCLK53: IC54.P$16, J108.2
BCLK54: IC55.P$16, J110.2
BCLK55: IC56.P$16, J112.2
BCLK56: IC57.P$16, J114.2
BCLK57: IC58.P$16, J116.2
BCLK58: IC59.P$16, J118.2
BCLK59: IC60.P$16, J120.2
BCLK60: IC61.P$16, J122.2
BCLK61: IC62.P$16, J124.2
BCLK62: IC63.P$16, J126.2
BCLK63: IC64.P$16, J128.2
BCLK64: IC65.P$16, J130.2
BCLK65: IC66.P$16, J132.2
BCLK66: IC67.P$16, J134.2
BCLK67: IC68.P$16, J136.2
BCLK68: IC69.P$16, J138.2
BCLK69: IC70.P$16, J140.2
DIN: IC1.P$1, J2.3
DIN1: IC2.P$1, J4.3
DIN2: IC3.P$1, J6.3
DIN3: IC4.P$1, J8.3
DIN4: IC5.P$1, J10.3
DIN5: IC6.P$1, J12.3
DIN6: IC7.P$1, J14.3
DIN7: IC8.P$1, J16.3
DIN8: IC9.P$1, J18.3
DIN9: IC10.P$1, J20.3
DIN10: IC11.P$1, J22.3
DIN11: IC12.P$1, J24.3
DIN12: IC13.P$1, J26.3
DIN13: IC14.P$1, J28.3
DIN14: IC15.P$1, J30.3
DIN15: IC16.P$1, J32.3
DIN16: IC17.P$1, J34.3
DIN17: IC18.P$1, J36.3
DIN18: IC19.P$1, J38.3
DIN19: IC20.P$1, J40.3
DIN20: IC21.P$1, J42.3
DIN21: IC22.P$1, J44.3
DIN22: IC23.P$1, J46.3
DIN23: IC24.P$1, J48.3
DIN24: IC25.P$1, J50.3
DIN25: IC26.P$1, J52.3
DIN26: IC27.P$1, J54.3
DIN27: IC28.P$1, J56.3
DIN28: IC29.P$1, J58.3
DIN29: IC30.P$1, J60.3
DIN30: IC31.P$1, J62.3
DIN31: IC32.P$1, J64.3
DIN32: IC33.P$1, J66.3
DIN33: IC34.P$1, J68.3
DIN34: IC35.P$1, J70.3
DIN35: IC36.P$1, J72.3
DIN36: IC37.P$1, J74.3
DIN37: IC38.P$1, J76.3
DIN38: IC39.P$1, J78.3
DIN39: IC40.P$1, J80.3
DIN40: IC41.P$1, J82.3
DIN41: IC42.P$1, J84.3
DIN42: IC43.P$1, J86.3
DIN43: IC44.P$1, J88.3
DIN44: IC45.P$1, J90.3
DIN45: IC46.P$1, J92.3
DIN46: IC47.P$1, J94.3
DIN47: IC48.P$1, J96.3
DIN48: IC49.P$1, J98.3
DIN49: IC50.P$1, J100.3
DIN50: IC51.P$1, J102.3
DIN51: IC52.P$1, J104.3
DIN52: IC53.P$1, J106.3
DIN53: IC54.P$1, J108.3
DIN54: IC55.P$1, J110.3
DIN55: IC56.P$1, J112.3
DIN56: IC57.P$1, J114.3
DIN57: IC58.P$1, J116.3
DIN58: IC59.P$1, J118.3
DIN59: IC60.P$1, J120.3
DIN60: IC61.P$1, J122.3
DIN61: IC62.P$1, J124.3
DIN62: IC63.P$1, J126.3
DIN63: IC64.P$1, J128.3
DIN64: IC65.P$1, J130.3
DIN65: IC66.P$1, J132.3
DIN66: IC67.P$1, J134.3
DIN67: IC68.P$1, J136.3
DIN68: IC69.P$1, J138.3
DIN69: IC70.P$1, J140.3
GAIN: IC1.P$2, J2.4
GAIN1: IC2.P$2, J4.4
GAIN2: IC3.P$2, J6.4
GAIN3: IC4.P$2, J8.4
GAIN4: IC5.P$2, J10.4
GAIN5: IC6.P$2, J12.4
GAIN6: IC7.P$2, J14.4
GAIN7: IC8.P$2, J16.4
GAIN8: IC9.P$2, J18.4
GAIN9: IC10.P$2, J20.4
GAIN10: IC11.P$2, J22.4
GAIN11: IC12.P$2, J24.4
GAIN12: IC13.P$2, J26.4
GAIN13: IC14.P$2, J28.4
GAIN14: IC15.P$2, J30.4
GAIN15: IC16.P$2, J32.4
GAIN16: IC17.P$2, J34.4
GAIN17: IC18.P$2, J36.4
GAIN18: IC19.P$2, J38.4
GAIN19: IC20.P$2, J40.4
GAIN20: IC21.P$2, J42.4
GAIN21: IC22.P$2, J44.4
GAIN22: IC23.P$2, J46.4
GAIN23: IC24.P$2, J48.4
GAIN24: IC25.P$2, J50.4
GAIN25: IC26.P$2, J52.4
GAIN26: IC27.P$2, J54.4
GAIN27: IC28.P$2, J56.4
GAIN28: IC29.P$2, J58.4
GAIN29: IC30.P$2, J60.4
GAIN30: IC31.P$2, J62.4
GAIN31: IC32.P$2, J64.4
GAIN32: IC33.P$2, J66.4
GAIN33: IC34.P$2, J68.4
GAIN34: IC35.P$2, J70.4
GAIN35: IC36.P$2, J72.4
GAIN36: IC37.P$2, J74.4
GAIN37: IC38.P$2, J76.4
GAIN38: IC39.P$2, J78.4
GAIN39: IC40.P$2, J80.4
GAIN40: IC41.P$2, J82.4
GAIN41: IC42.P$2, J84.4
GAIN42: IC43.P$2, J86.4
GAIN43: IC44.P$2, J88.4
GAIN44: IC45.P$2, J90.4
GAIN45: IC46.P$2, J92.4
GAIN46: IC47.P$2, J94.4
GAIN47: IC48.P$2, J96.4
GAIN48: IC49.P$2, J98.4
GAIN49: IC50.P$2, J100.4
GAIN50: IC51.P$2, J102.4
GAIN51: IC52.P$2, J104.4
GAIN52: IC53.P$2, J106.4
GAIN53: IC54.P$2, J108.4
GAIN54: IC55.P$2, J110.4
GAIN55: IC56.P$2, J112.4
GAIN56: IC57.P$2, J114.4
GAIN57: IC58.P$2, J116.4
GAIN58: IC59.P$2, J118.4
GAIN59: IC60.P$2, J120.4
GAIN60: IC61.P$2, J122.4
GAIN61: IC62.P$2, J124.4
GAIN62: IC63.P$2, J126.4
GAIN63: IC64.P$2, J128.4
GAIN64: IC65.P$2, J130.4
GAIN65: IC66.P$2, J132.4
GAIN66: IC67.P$2, J134.4
GAIN67: IC68.P$2, J136.4
GAIN68: IC69.P$2, J138.4
GAIN69: IC70.P$2, J140.4
GND: C1.2, C2.2, IC1.P$3, IC1.P$11, IC1.P$15, IC1.P$EP, J2.6
GND1: C3.2, C4.2, IC2.P$3, IC2.P$11, IC2.P$15, IC2.P$EP, J4.6
GND2: C5.2, C6.2, IC3.P$3, IC3.P$11, IC3.P$15, IC3.P$EP, J6.6
GND3: C7.2, C8.2, IC4.P$3, IC4.P$11, IC4.P$15, IC4.P$EP, J8.6
GND4: C9.2, C10.2, IC5.P$3, IC5.P$11, IC5.P$15, IC5.P$EP, J10.6
GND5: C11.2, C12.2, IC6.P$3, IC6.P$11, IC6.P$15, IC6.P$EP, J12.6
GND6: C13.2, C14.2, IC7.P$3, IC7.P$11, IC7.P$15, IC7.P$EP, J14.6
GND7: C15.2, C16.2, IC8.P$3, IC8.P$11, IC8.P$15, IC8.P$EP, J16.6
GND8: C17.2, C18.2, IC9.P$3, IC9.P$11, IC9.P$15, IC9.P$EP, J18.6
GND9: C19.2, C20.2, IC10.P$3, IC10.P$11, IC10.P$15, IC10.P$EP, J20.6
GND10: C21.2, C22.2, IC11.P$3, IC11.P$11, IC11.P$15, IC11.P$EP, J22.6
GND11: C23.2, C24.2, IC12.P$3, IC12.P$11, IC12.P$15, IC12.P$EP, J24.6
GND12: C25.2, C26.2, IC13.P$3, IC13.P$11, IC13.P$15, IC13.P$EP, J26.6
GND13: C27.2, C28.2, IC14.P$3, IC14.P$11, IC14.P$15, IC14.P$EP, J28.6
GND14: C29.2, C30.2, IC15.P$3, IC15.P$11, IC15.P$15, IC15.P$EP, J30.6
GND15: C31.2, C32.2, IC16.P$3, IC16.P$11, IC16.P$15, IC16.P$EP, J32.6
GND16: C33.2, C34.2, IC17.P$3, IC17.P$11, IC17.P$15, IC17.P$EP, J34.6
GND17: C35.2, C36.2, IC18.P$3, IC18.P$11, IC18.P$15, IC18.P$EP, J36.6
GND18: C37.2, C38.2, IC19.P$3, IC19.P$11, IC19.P$15, IC19.P$EP, J38.6
GND19: C39.2, C40.2, IC20.P$3, IC20.P$11, IC20.P$15, IC20.P$EP, J40.6
GND20: C41.2, C42.2, IC21.P$3, IC21.P$11, IC21.P$15, IC21.P$EP, J42.6
GND21: C43.2, C44.2, IC22.P$3, IC22.P$11, IC22.P$15, IC22.P$EP, J44.6
GND22: C45.2, C46.2, IC23.P$3, IC23.P$11, IC23.P$15, IC23.P$EP, J46.6
GND23: C47.2, C48.2, IC24.P$3, IC24.P$11, IC24.P$15, IC24.P$EP, J48.6
GND24: C49.2, C50.2, IC25.P$3, IC25.P$11, IC25.P$15, IC25.P$EP, J50.6
GND25: C51.2, C52.2, IC26.P$3, IC26.P$11, IC26.P$15, IC26.P$EP, J52.6
GND26: C53.2, C54.2, IC27.P$3, IC27.P$11, IC27.P$15, IC27.P$EP, J54.6
GND27: C55.2, C56.2, IC28.P$3, IC28.P$11, IC28.P$15, IC28.P$EP, J56.6
GND28: C57.2, C58.2, IC29.P$3, IC29.P$11, IC29.P$15, IC29.P$EP, J58.6
GND29: C59.2, C60.2, IC30.P$3, IC30.P$11, IC30.P$15, IC30.P$EP, J60.6
GND30: C61.2, C62.2, IC31.P$3, IC31.P$11, IC31.P$15, IC31.P$EP, J62.6
GND31: C63.2, C64.2, IC32.P$3, IC32.P$11, IC32.P$15, IC32.P$EP, J64.6
GND32: C65.2, C66.2, IC33.P$3, IC33.P$11, IC33.P$15, IC33.P$EP, J66.6
GND33: C67.2, C68.2, IC34.P$3, IC34.P$11, IC34.P$15, IC34.P$EP, J68.6
GND34: C69.2, C70.2, IC35.P$3, IC35.P$11, IC35.P$15, IC35.P$EP, J70.6
GND35: C71.2, C72.2, IC36.P$3, IC36.P$11, IC36.P$15, IC36.P$EP, J72.6
GND36: C73.2, C74.2, IC37.P$3, IC37.P$11, IC37.P$15, IC37.P$EP, J74.6
GND37: C75.2, C76.2, IC38.P$3, IC38.P$11, IC38.P$15, IC38.P$EP, J76.6
GND38: C77.2, C78.2, IC39.P$3, IC39.P$11, IC39.P$15, IC39.P$EP, J78.6
GND39: C79.2, C80.2, IC40.P$3, IC40.P$11, IC40.P$15, IC40.P$EP, J80.6
GND40: C81.2, C82.2, IC41.P$3, IC41.P$11, IC41.P$15, IC41.P$EP, J82.6
GND41: C83.2, C84.2, IC42.P$3, IC42.P$11, IC42.P$15, IC42.P$EP, J84.6
GND42: C85.2, C86.2, IC43.P$3, IC43.P$11, IC43.P$15, IC43.P$EP, J86.6
GND43: C87.2, C88.2, IC44.P$3, IC44.P$11, IC44.P$15, IC44.P$EP, J88.6
GND44: C89.2, C90.2, IC45.P$3, IC45.P$11, IC45.P$15, IC45.P$EP, J90.6
GND45: C91.2, C92.2, IC46.P$3, IC46.P$11, IC46.P$15, IC46.P$EP, J92.6
GND46: C93.2, C94.2, IC47.P$3, IC47.P$11, IC47.P$15, IC47.P$EP, J94.6
GND47: C95.2, C96.2, IC48.P$3, IC48.P$11, IC48.P$15, IC48.P$EP, J96.6
GND48: C97.2, C98.2, IC49.P$3, IC49.P$11, IC49.P$15, IC49.P$EP, J98.6
GND49: C99.2, C100.2, IC50.P$3, IC50.P$11, IC50.P$15, IC50.P$EP, J100.6
GND50: C101.2, C102.2, IC51.P$3, IC51.P$11, IC51.P$15, IC51.P$EP, J102.6
GND51: C103.2, C104.2, IC52.P$3, IC52.P$11, IC52.P$15, IC52.P$EP, J104.6
GND52: C105.2, C106.2, IC53.P$3, IC53.P$11, IC53.P$15, IC53.P$EP, J106.6
GND53: C107.2, C108.2, IC54.P$3, IC54.P$11, IC54.P$15, IC54.P$EP, J108.6
GND54: C109.2, C110.2, IC55.P$3, IC55.P$11, IC55.P$15, IC55.P$EP, J110.6
GND55: C111.2, C112.2, IC56.P$3, IC56.P$11, IC56.P$15, IC56.P$EP, J112.6
GND56: C113.2, C114.2, IC57.P$3, IC57.P$11, IC57.P$15, IC57.P$EP, J114.6
GND57: C115.2, C116.2, IC58.P$3, IC58.P$11, IC58.P$15, IC58.P$EP, J116.6
GND58: C117.2, C118.2, IC59.P$3, IC59.P$11, IC59.P$15, IC59.P$EP, J118.6
GND59: C119.2, C120.2, IC60.P$3, IC60.P$11, IC60.P$15, IC60.P$EP, J120.6
GND60: C121.2, C122.2, IC61.P$3, IC61.P$11, IC61.P$15, IC61.P$EP, J122.6
GND61: C123.2, C124.2, IC62.P$3, IC62.P$11, IC62.P$15, IC62.P$EP, J124.6
GND62: C125.2, C126.2, IC63.P$3, IC63.P$11, IC63.P$15, IC63.P$EP, J126.6
GND63: C127.2, C128.2, IC64.P$3, IC64.P$11, IC64.P$15, IC64.P$EP, J128.6
GND64: C129.2, C130.2, IC65.P$3, IC65.P$11, IC65.P$15, IC65.P$EP, J130.6
GND65: C131.2, C132.2, IC66.P$3, IC66.P$11, IC66.P$15, IC66.P$EP, J132.6
GND66: C133.2, C134.2, IC67.P$3, IC67.P$11, IC67.P$15, IC67.P$EP, J134.6
GND67: C135.2, C136.2, IC68.P$3, IC68.P$11, IC68.P$15, IC68.P$EP, J136.6
GND68: C137.2, C138.2, IC69.P$3, IC69.P$11, IC69.P$15, IC69.P$EP, J138.6
GND69: C139.2, C140.2, IC70.P$3, IC70.P$11, IC70.P$15, IC70.P$EP, J140.6
LRCLK: IC1.P$14, J2.1
LRCLK1: IC2.P$14, J4.1
LRCLK2: IC3.P$14, J6.1
LRCLK3: IC4.P$14, J8.1
LRCLK4: IC5.P$14, J10.1
LRCLK5: IC6.P$14, J12.1
LRCLK6: IC7.P$14, J14.1
LRCLK7: IC8.P$14, J16.1
LRCLK8: IC9.P$14, J18.1
LRCLK9: IC10.P$14, J20.1
LRCLK10: IC11.P$14, J22.1
LRCLK11: IC12.P$14, J24.1
LRCLK12: IC13.P$14, J26.1
LRCLK13: IC14.P$14, J28.1
LRCLK14: IC15.P$14, J30.1
LRCLK15: IC16.P$14, J32.1
LRCLK16: IC17.P$14, J34.1
LRCLK17: IC18.P$14, J36.1
LRCLK18: IC19.P$14, J38.1
LRCLK19: IC20.P$14, J40.1
LRCLK20: IC21.P$14, J42.1
LRCLK21: IC22.P$14, J44.1
LRCLK22: IC23.P$14, J46.1
LRCLK23: IC24.P$14, J48.1
LRCLK24: IC25.P$14, J50.1
LRCLK25: IC26.P$14, J52.1
LRCLK26: IC27.P$14, J54.1
LRCLK27: IC28.P$14, J56.1
LRCLK28: IC29.P$14, J58.1
LRCLK29: IC30.P$14, J60.1
LRCLK30: IC31.P$14, J62.1
LRCLK31: IC32.P$14, J64.1
LRCLK32: IC33.P$14, J66.1
LRCLK33: IC34.P$14, J68.1
LRCLK34: IC35.P$14, J70.1
LRCLK35: IC36.P$14, J72.1
LRCLK36: IC37.P$14, J74.1
LRCLK37: IC38.P$14, J76.1
LRCLK38: IC39.P$14, J78.1
LRCLK39: IC40.P$14, J80.1
LRCLK40: IC41.P$14, J82.1
LRCLK41: IC42.P$14, J84.1
LRCLK42: IC43.P$14, J86.1
LRCLK43: IC44.P$14, J88.1
LRCLK44: IC45.P$14, J90.1
LRCLK45: IC46.P$14, J92.1
LRCLK46: IC47.P$14, J94.1
LRCLK47: IC48.P$14, J96.1
LRCLK48: IC49.P$14, J98.1
LRCLK49: IC50.P$14, J100.1
LRCLK50: IC51.P$14, J102.1
LRCLK51: IC52.P$14, J104.1
LRCLK52: IC53.P$14, J106.1
LRCLK53: IC54.P$14, J108.1
LRCLK54: IC55.P$14, J110.1
LRCLK55: IC56.P$14, J112.1
LRCLK56: IC57.P$14, J114.1
LRCLK57: IC58.P$14, J116.1
LRCLK58: IC59.P$14, J118.1
LRCLK59: IC60.P$14, J120.1
LRCLK60: IC61.P$14, J122.1
LRCLK61: IC62.P$14, J124.1
LRCLK62: IC63.P$14, J126.1
LRCLK63: IC64.P$14, J128.1
LRCLK64: IC65.P$14, J130.1
LRCLK65: IC66.P$14, J132.1
LRCLK66: IC67.P$14, J134.1
LRCLK67: IC68.P$14, J136.1
LRCLK68: IC69.P$14, J138.1
LRCLK69: IC70.P$14, J140.1
unnamed: JP3.3, R3.1
unnamed: JP4.2, R4.1
unnamed: JP5.3, R5.1
unnamed: JP6.2, R6.1
unnamed: JP7.3, R7.1
unnamed: JP8.2, R8.1
unnamed: JP2.2, R2.1
unnamed: JP9.3, R9.1
unnamed: JP1.3, R1.1
unnamed: JP10.2, R10.1
unnamed: JP11.3, R11.1
unnamed: JP12.2, R12.1
unnamed: JP13.3, R13.1
unnamed: JP14.2, R14.1
unnamed: JP15.3, R15.1
unnamed: JP16.2, R16.1
unnamed: JP17.3, R17.1
unnamed: JP18.2, R18.1
unnamed: JP19.3, R19.1
unnamed: JP20.2, R20.1
unnamed: JP21.3, R21.1
unnamed: JP22.2, R22.1
unnamed: JP23.3, R23.1
unnamed: JP24.2, R24.1
unnamed: JP25.3, R25.1
unnamed: JP26.2, R26.1
unnamed: JP27.3, R27.1
unnamed: JP28.2, R28.1
unnamed: JP29.3, R29.1
unnamed: JP30.2, R30.1
unnamed: JP31.3, R31.1
unnamed: JP32.2, R32.1
unnamed: JP33.3, R33.1
unnamed: JP34.2, R34.1
unnamed: JP35.3, R35.1
unnamed: JP36.2, R36.1
unnamed: JP37.3, R37.1
unnamed: JP38.2, R38.1
unnamed: JP39.3, R39.1
unnamed: JP40.2, R40.1
unnamed: JP41.3, R41.1
unnamed: JP42.2, R42.1
unnamed: JP43.3, R43.1
unnamed: JP44.2, R44.1
unnamed: JP45.3, R45.1
unnamed: JP46.2, R46.1
unnamed: JP47.3, R47.1
unnamed: JP48.2, R48.1
unnamed: JP49.3, R49.1
unnamed: JP50.2, R50.1
unnamed: JP51.3, R51.1
unnamed: JP52.2, R52.1
unnamed: JP53.3, R53.1
unnamed: JP54.2, R54.1
unnamed: JP55.3, R55.1
unnamed: JP56.2, R56.1
unnamed: JP57.3, R57.1
unnamed: JP58.2, R58.1
unnamed: JP59.3, R59.1
unnamed: JP60.2, R60.1
unnamed: JP61.3, R61.1
unnamed: JP62.2, R62.1
unnamed: JP63.3, R63.1
unnamed: JP64.2, R64.1
unnamed: JP65.3, R65.1
unnamed: JP66.2, R66.1
unnamed: JP67.3, R67.1
unnamed: JP68.2, R68.1
unnamed: JP69.3, R69.1
unnamed: JP70.2, R70.1
unnamed: JP71.3, R71.1
unnamed: JP72.2, R72.1
unnamed: JP73.3, R73.1
unnamed: JP74.2, R74.1
unnamed: JP75.3, R75.1
unnamed: JP76.2, R76.1
unnamed: JP77.3, R77.1
unnamed: JP78.2, R78.1
unnamed: JP79.3, R79.1
unnamed: JP80.2, R80.1
unnamed: JP81.3, R81.1
unnamed: JP82.2, R82.1
unnamed: JP83.3, R83.1
unnamed: JP84.2, R84.1
unnamed: JP85.3, R85.1
unnamed: JP86.2, R86.1
unnamed: JP87.3, R87.1
unnamed: JP88.2, R88.1
unnamed: JP89.3, R89.1
unnamed: JP90.2, R90.1
unnamed: JP91.3, R91.1
unnamed: JP92.2, R92.1
unnamed: JP93.3, R93.1
unnamed: JP94.2, R94.1
unnamed: JP95.3, R95.1
unnamed: JP96.2, R96.1
unnamed: JP97.3, R97.1
unnamed: JP98.2, R98.1
unnamed: JP99.3, R99.1
unnamed: JP100.2, R100.1
unnamed: JP101.3, R101.1
unnamed: JP102.2, R102.1
unnamed: JP103.3, R103.1
unnamed: JP104.2, R104.1
unnamed: JP105.3, R105.1
unnamed: JP106.2, R106.1
unnamed: JP107.3, R107.1
unnamed: JP108.2, R108.1
unnamed: JP109.3, R109.1
unnamed: JP110.2, R110.1
unnamed: JP111.3, R111.1
unnamed: JP112.2, R112.1
unnamed: JP113.3, R113.1
unnamed: JP114.2, R114.1
unnamed: JP115.3, R115.1
unnamed: JP116.2, R116.1
unnamed: JP117.3, R117.1
unnamed: JP118.2, R118.1
unnamed: JP119.3, R119.1
unnamed: JP120.2, R120.1
unnamed: JP121.3, R121.1
unnamed: JP122.2, R122.1
unnamed: JP123.3, R123.1
unnamed: JP124.2, R124.1
unnamed: JP125.3, R125.1
unnamed: JP126.2, R126.1
unnamed: JP127.3, R127.1
unnamed: JP128.2, R128.1
unnamed: JP129.3, R129.1
unnamed: JP130.2, R130.1
unnamed: JP131.3, R131.1
unnamed: JP132.2, R132.1
unnamed: JP133.3, R133.1
unnamed: JP134.2, R134.1
unnamed: JP135.3, R135.1
unnamed: JP136.2, R136.1
unnamed: JP137.3, R137.1
unnamed: JP138.2, R138.1
unnamed: JP139.3, R139.1
unnamed: JP140.2, R140.1
OUT+: IC1.P$9, J1.1
OUT+1: IC2.P$9, J3.1
OUT+2: IC3.P$9, J5.1
OUT+3: IC4.P$9, J7.1
OUT+4: IC5.P$9, J9.1
OUT+5: IC6.P$9, J11.1
OUT+6: IC7.P$9, J13.1
OUT+7: IC8.P$9, J15.1
OUT+8: IC9.P$9, J17.1
OUT+9: IC10.P$9, J19.1
OUT+10: IC11.P$9, J21.1
OUT+11: IC12.P$9, J23.1
OUT+12: IC13.P$9, J25.1
OUT+13: IC14.P$9, J27.1
OUT+14: IC15.P$9, J29.1
OUT+15: IC16.P$9, J31.1
OUT+16: IC17.P$9, J33.1
OUT+17: IC18.P$9, J35.1
OUT+18: IC19.P$9, J37.1
OUT+19: IC20.P$9, J39.1
OUT+20: IC21.P$9, J41.1
OUT+21: IC22.P$9, J43.1
OUT+22: IC23.P$9, J45.1
OUT+23: IC24.P$9, J47.1
OUT+24: IC25.P$9, J49.1
OUT+25: IC26.P$9, J51.1
OUT+26: IC27.P$9, J53.1
OUT+27: IC28.P$9, J55.1
OUT+28: IC29.P$9, J57.1
OUT+29: IC30.P$9, J59.1
OUT+30: IC31.P$9, J61.1
OUT+31: IC32.P$9, J63.1
OUT+32: IC33.P$9, J65.1
OUT+33: IC34.P$9, J67.1
OUT+34: IC35.P$9, J69.1
OUT+35: IC36.P$9, J71.1
OUT+36: IC37.P$9, J73.1
OUT+37: IC38.P$9, J75.1
OUT+38: IC39.P$9, J77.1
OUT+39: IC40.P$9, J79.1
OUT+40: IC41.P$9, J81.1
OUT+41: IC42.P$9, J83.1
OUT+42: IC43.P$9, J85.1
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
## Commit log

2018-06-21 Initial Commit
    Added schematic and board files
2018-06-22 Design review changes
    Moved buzzard labels away from headers slightly
2018-06-25 Updated Bottom Silk
    Used new buzzard labels so the bottom of the board is more readable within Eagle.
2018-07-17 v10
    Removed + symbol on top copper
    Removed ferrite beads
2018-07-20 v10 panel
2018-08-29 Fixed IC1 Value
    -Fixed IC1 value from MAX98375A to MAX98357A
2018-09-05 Repo Cleanup
    - Moved board files into /Hardware folder
    - Updated readme
